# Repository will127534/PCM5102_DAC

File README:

PCM5102 DAC layout using eagle pcb

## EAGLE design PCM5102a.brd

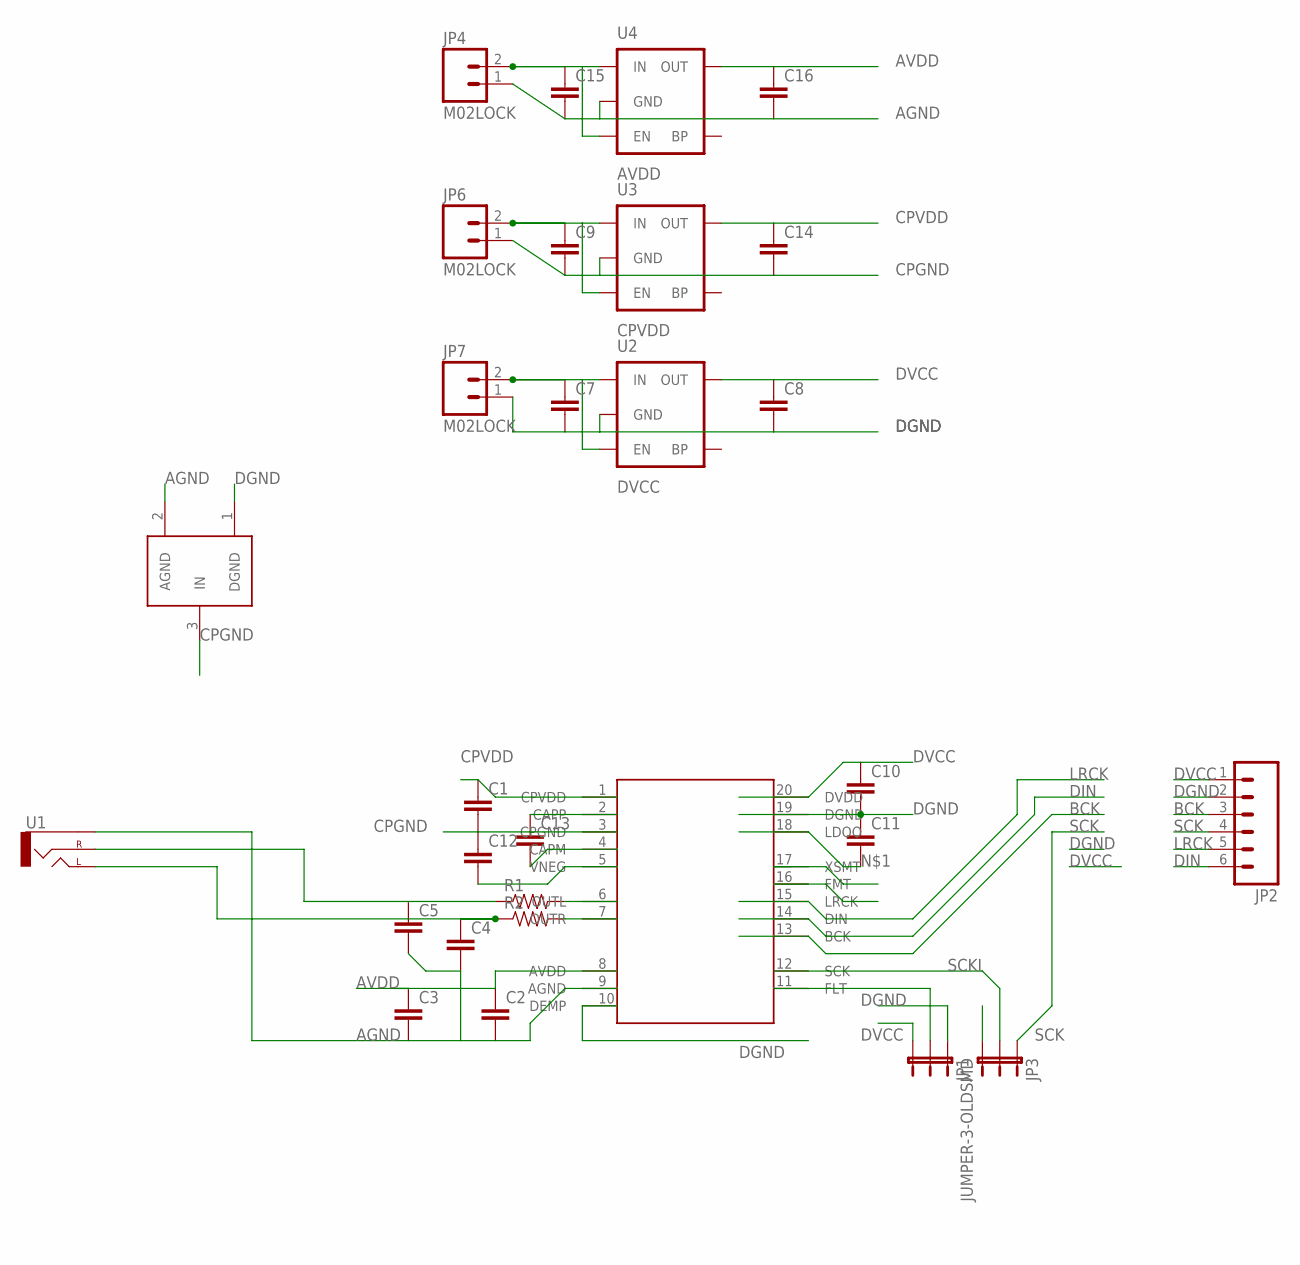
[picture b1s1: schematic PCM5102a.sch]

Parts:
C1, C2, C3, C7, C8, C9, C10, C11, C12, C13, C14, C15, C16: CAP0805; 0805
C4, C5: CAPPTH1; CAP-PTH-5MM
JP1: JUMPER-3-OLDPTH; 1X03
JP2: M06LOCK; 1X06_LOCK
JP3: JUMPER-3-OLDSMD; SJ_3
JP4, JP6, JP7: M02LOCK; 1X02_LOCK
R1, R2: RESISTORPTH-1/4W; AXIAL-0.4
U1: AUDIO-JACKPTH; AUDIO-JACK
U2: DVCC; SOT23-5
U3: CPVDD; SOT23-5
U4: AVDD; SOT23-5
U$1: PCM5102; TSSOP20
U$2: GND_CONNECT

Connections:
AGND: C2.2, C3.2, C4.2, C5.2, C15.2, C16.2, JP4.1, U1.SLEEVE, U4.2 (GND), U$1.9 (AGND), U$2.2 (AGND)
AVDD: C2.1, C3.1, C16.1, U4.5 (OUT), U$1.8 (AVDD)
BCK: JP2.3, U$1.13 (BCK)
CPGND: C1.2, C9.2, C12.1, C14.2, JP6.1, U3.2 (GND), U$1.3 (CPGND), U$2.3 (IN)
CPVDD: C1.1, C14.1, U3.5 (OUT), U$1.1 (CPVDD)
DGND: C7.2, C8.2, C10.2, C11.1, JP1.1, JP2.2, JP3.3, JP7.1, U2.2 (GND), U$1.10 (DEMP), U$1.16 (FMT), U$1.19 (DGND), U$2.1 (DGND)
DIN: JP2.6, U$1.14 (DIN)
DVCC: C8.1, C10.1, JP1.3, JP2.1, U2.5 (OUT), U$1.17 (XSMT), U$1.20 (DVDD)
LRCK: JP2.5, U$1.15 (LRCK)
unnamed: C11.2, U$1.18 (LDOO)
unnamed: R1.P$2 (2), U$1.6 (OUTL)
unnamed: JP1.2, U$1.11 (FLT)
unnamed: C13.1, U$1.2 (CAPP)
unnamed: C13.2, U$1.4 (CAPM)
unnamed: C12.2, U$1.5 (VNEG)
unnamed: R2.P$2 (2), U$1.7 (OUTR)
unnamed: C15.1, JP4.2, U4.1 (IN), U4.3 (EN)
unnamed: C5.1, R1.P$1 (1), U1.RING (RIGHT)
unnamed: C4.1, R2.P$1 (1), U1.TIP (LEFT)
unnamed: C9.1, JP6.2, U3.1 (IN), U3.3 (EN)
unnamed: C7.1, JP7.2, U2.1 (IN), U2.3 (EN)
SCK: JP2.4, JP3.1
SCKI: JP3.2, U$1.12 (SCK)

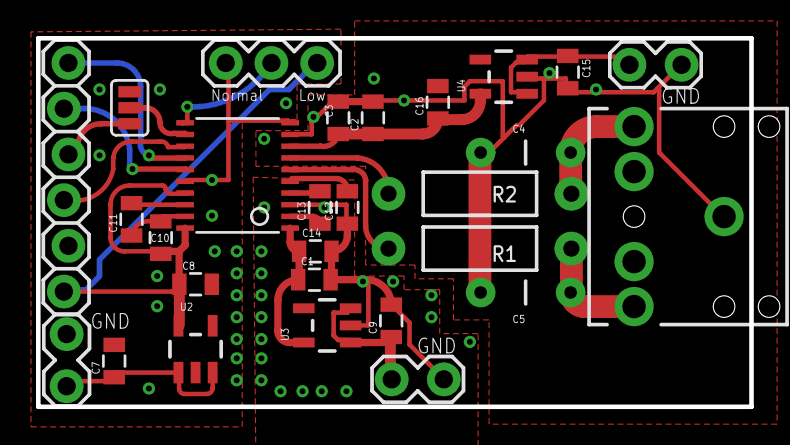
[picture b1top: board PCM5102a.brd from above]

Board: 2 copper layers, 39.6 x 20.5 mm, 29 parts (1 on the bottom side), 23 nets.

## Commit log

2013-12-28 V1.0
2013-12-28 V1.1
    fix DVDD DVCC connection
2013-12-28 v1.1
2014-01-07 V1.2
    Change LDO from LM1117 to LP5907 (Ultra Low noise)
2014-01-08 V1.21

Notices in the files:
parts and their libraries:
SparkFun-Capacitors: Licensing: CC v3.0 Share-Alike You are welcome to use this library for commercial purposes.
